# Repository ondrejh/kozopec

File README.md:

msp430 based stepper driver logic
=================================

## Description

The device is using small mcu to generate pulses for stepper driver. It has 3 digital inputs (forward, backward and release), one analog input (speed) and 3 outputs (PUL, DIR, ENA). The speed (frequency of the pulses) follows ramps to make start and stop softer. If the release input is active, the motor is released (no current) when its stopped.

## Prototype and programmer

Insert image here ..

## Second prototype

Insert image here ..

TODO:
1) vyzkouset
2) doplnit dokumentaci

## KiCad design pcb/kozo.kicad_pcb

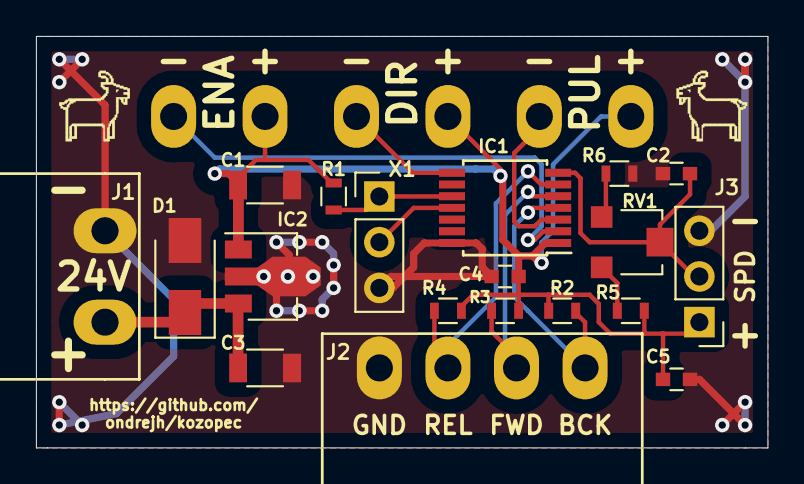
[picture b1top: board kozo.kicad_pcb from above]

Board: 2 copper layers, 40.6 x 22.9 mm, 22 parts (1 on the bottom side), 14 nets.

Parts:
C1: 4u7; C_1206
C2, C4, C5: 100n; C_0603
C3: 1u0/35V; C_1206
D1: SMAJ33A; D_SMA
IC1: MSP430G2231IPW14; TSSOP-14_4.4x5mm_Pitch0.65mm
IC2: L78L33_SOT89; SOT-89-3
J1: Conn_01x02; PA257_508_02
J2: Conn_01x04; PA357_381_04
J3: Conn_01x03; Pin_Header_Straight_1x03_Pitch2.54mm
J4: Conn_01x06; PA257_508_06
LOGO: koza
LOGO#2: koza_inv
R1, R2, R3, R4: 10k; R_0603
R5, R6: 4k7; R_0603
RV1: 50k; Potentiometer_Trimmer-EVM3E
X1: Conn_01x03; Pin_Header_Straight_1x03_Pitch2.54mm

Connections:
+3V3: C1.1, C4.1, C5.1, IC1.1, IC2.1, J3.1, J4.2, J4.4, J4.6, R1.1, R2.1, R3.1, R4.1, R5.1
GND: C1.2, C2.2, C3.2, C4.2, C5.2, D1.2, IC1.14, IC2.2, J1.1, J2.1, J3.3, R6.2, X1.3
unnamed: C2.1, IC1.7, J3.2, RV1.2
unnamed: C3.1, D1.1, IC2.3, J1.2
unnamed: IC1.2, J4.1
unnamed: IC1.3, J4.5
unnamed: IC1.4, J2.4, R2.2
unnamed: IC1.5, J2.3, R3.2
unnamed: IC1.6, J2.2, R4.2
unnamed: IC1.8, J4.3
unnamed: IC1.11, X1.2
unnamed: R5.2, RV1.3
unnamed: R6.1, RV1.1
RESET: IC1.10, R1.2, X1.1

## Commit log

2014-02-28 project cleanup
2014-02-28 cb project renamed
2014-02-28 hw is ready to code
2014-03-03 pwm dimming
2014-03-03 readme update
2014-03-03 debug pwm, some blinking artwork
2014-03-06 basic 25/5min timing
2014-03-09 button works
2015-06-04 mcu msp430g2452
2020-06-24 basic function
2020-06-26 forwar, backward, release button and some docu
2020-06-26 smaller mcu
2020-06-27 dirrection tested
2020-06-28 speed controll
2020-07-01 holder scatch
2020-07-02 holder drawing
2020-07-02 pwon stopped
2020-07-03 schematic
2020-07-08 basic layout
2020-07-08 layout
2020-07-10 silkscreen
2020-07-10 nice schmatic
2020-07-10 silk goat
2020-07-10 mask debug
2020-07-10 gerber data
2020-07-10 pcb folder renamed
2020-07-20 release not
2020-07-21 interactive layout
2020-07-21 push button mode
2021-05-06 new compiler
2021-05-06 ignore list update
2021-05-06 gerber data archive
2021-09-08 small holder for smaler motor
2021-09-08 more parts
